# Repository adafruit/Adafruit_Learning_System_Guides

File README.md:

# Introduction

This is a collection of smaller programs and scripts to display "inline" in [Adafruit Learning System][learn] guides.

Adafruit is an Open Source company. To support Adafruit, please consider buying products at [adafruit.com](https://www.adafruit.com/).

Starting in 2023, guides using a specific Adafruit board will be placed in a subdirectory with that product name to reduce the number of directories under the main directory. If you are creating a new guide, please check if your Adafruit board falls into one of these groups and make your project code directory in the appropriate subfolder.

* Flora/
* ItsyBitsy/
* MagTag/
* MEMENTO/
* NeoTrellis/
* PyLeap/
* PyPortal/
* QTPy/
* Metro/ (all types)
* Matrix_Portal/
* Crickits/
* Gemma/ (both types)

If a new product or project group is contemplated, contact Learn moderators for guidance.

## Issues

Issues with guides should be reported in the guide itself under "Feedback? Corrections?"

## Make Your Own Guides

This repo is only for Adafruit approved Learning System Guides. If you'd like to write your own guide, see [Create your own content with Adafruit Playground!](https://learn.adafruit.com/adafruit-playground-notes).

## Contributing and Testing

For details on contributing for Adafruit approved guides, see the guide [Contribute to the Adafruit Learning System with Git and GitHub](https://learn.adafruit.com/contribute-to-the-adafruit-learning-system-with-git-and-github) and [Contribute to CircuitPython with Git and GitHub](https://learn.adafruit.com/contribute-to-circuitpython-with-git-and-github/github-personal-access-token).

The code here is checked by GitHub Actions against Pylint (for CircuitPython code) or the Arduino compilation process.

Code in directories containing a file called `.circuitpython.skip` will be skipped by Pylint checks.

Code in directories containing a `.[platformname].test` file, such as `.uno.test` will be compiled against the corresponding platform.

[learn]: https://learn.adafruit.com/

## Running pylint locally
Install a specific version of pylint under the name "pylint-learn":
```
pip install pipx
pipx install --suffix=-learn pylint==2.7.1
```
Then use the `pylint_check` script to run pylint on the files or directories
of your choice (note that your terminal *must* be in the top directory of
Adafruit_Learning_System_Guides, not a sub-directory):
```
./pylint_check CircuitPython_Cool_Project
```
## Licensing

Adafruit Learning System code files should have author and license information conforming to the open [SPDX specification](https://www.iso.org/standard/81870.html).
See [this page](https://learn.adafruit.com/contribute-to-the-adafruit-learning-system-with-git-and-github/add-author-and-license-information) for more.

Updated November 18, 2025

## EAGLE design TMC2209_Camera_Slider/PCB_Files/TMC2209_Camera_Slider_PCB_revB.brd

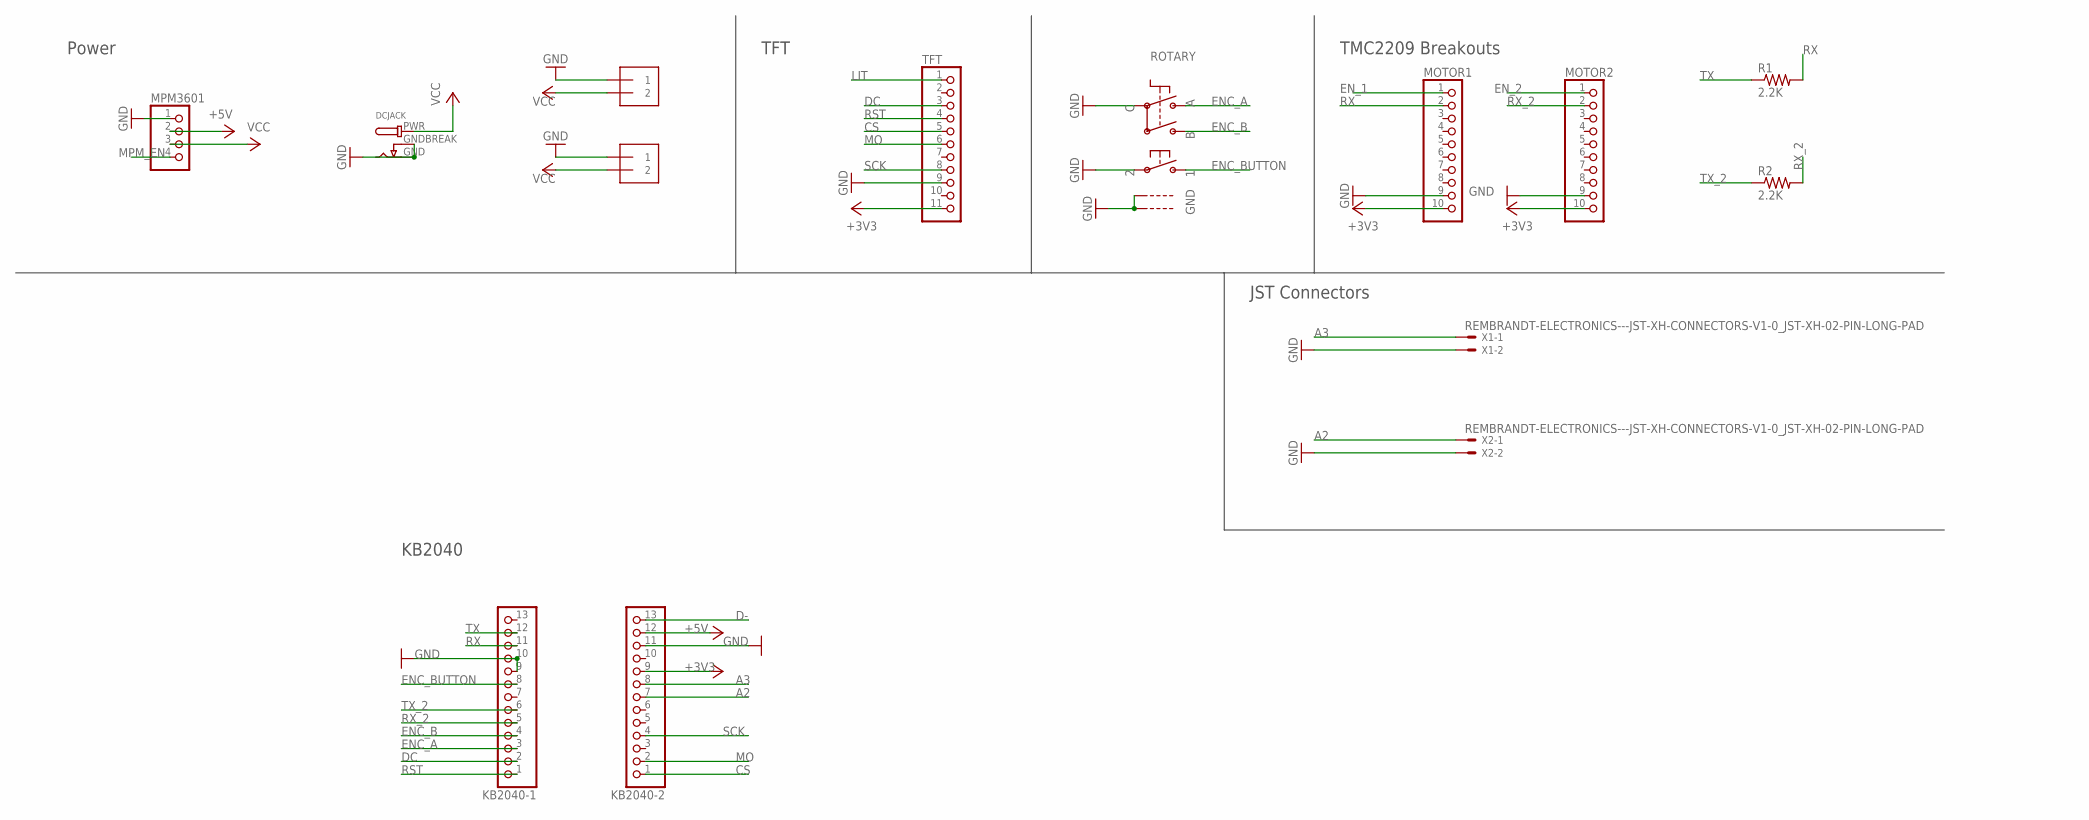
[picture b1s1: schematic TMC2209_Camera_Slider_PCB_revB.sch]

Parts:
DCJACK: DCBARRELPTH; DCJACK_2MM_PTH
J1, J2: 1X2-3.5MM
KB2040-1, KB2040-2: HEADER-1X13; 1X13_ROUND_70
MOTOR1, MOTOR2: HEADER-1X10; 1X10_OVAL
MPM3601: HEADER-1X4; 1X04_OVAL
R1, R2: 2.2K; 0309/12
ROTARY: ENCODER_PLUS_SWITCH_BOURNS_PEC11; PEC11+SWITCH
TFT: HEADER-1X11; 1X11_ROUND
X1, X2: REMBRANDT-ELECTRONICS---JST-XH-CONNECTORS-V1-0_JS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; REMBRANDT-ELECTRONICS---JST-XH-CONNECTORS-V1-0_JST-XH-02-PA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

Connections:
+3V3: KB2040-2.9, MOTOR1.10, MOTOR2.10, TFT.11
+5V: KB2040-2.12, MPM3601.2
A2: KB2040-2.7, X2.1
A3: KB2040-2.8, X1.1
CS: KB2040-2.1, TFT.5
D-: KB2040-2.13
DC: KB2040-1.2, TFT.3
ENC_A: KB2040-1.3, ROTARY.P$A
ENC_B: KB2040-1.4, ROTARY.P$B
ENC_BUTTON: KB2040-1.8, ROTARY.P$1
EN_1: MOTOR1.1
EN_2: MOTOR2.1
GND: DCJACK.GND, DCJACK.GNDBREAK, J1.1, J2.1, KB2040-1.9, KB2040-1.10, KB2040-2.11, MOTOR1.9, MOTOR2.9, MPM3601.1, ROTARY.P$2, ROTARY.P$C, ROTARY.P$GND1, ROTARY.P$GND2, TFT.9, X1.2, X2.2
LIT: TFT.1
MO: KB2040-2.2, TFT.6
MPM_EN: MPM3601.4
RST: KB2040-1.1, TFT.4
RX: KB2040-1.11, MOTOR1.2, R1.2
RX_2: KB2040-1.5, MOTOR2.2, R2.2
SCK: KB2040-2.4, TFT.8
TX: KB2040-1.12, R1.1
TX_2: KB2040-1.6, R2.1
VCC: DCJACK.PWR, J1.2, J2.2, MPM3601.3

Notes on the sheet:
Power
TFT
TMC2209 Breakouts
KB2040
JST Connectors

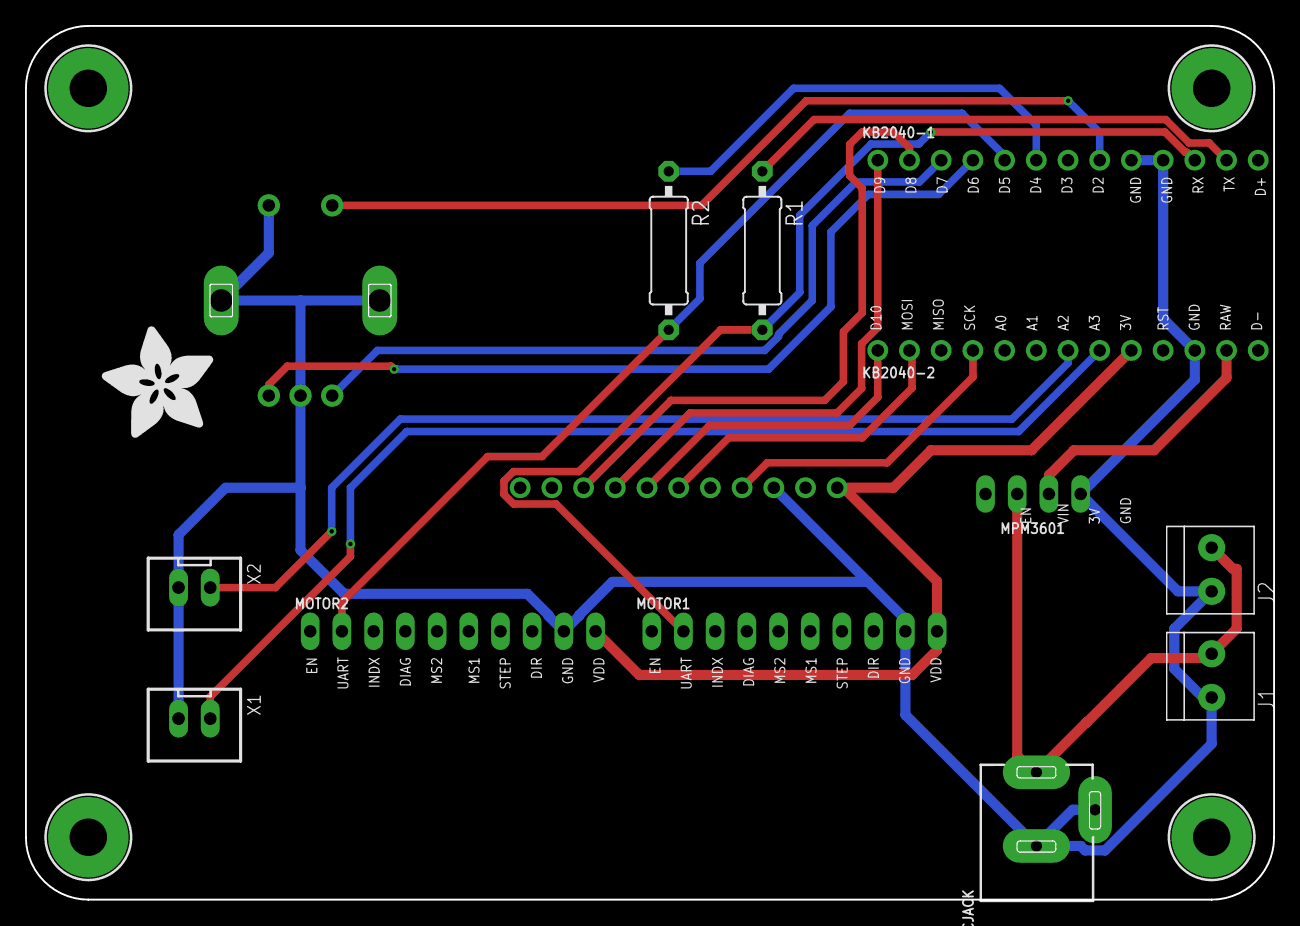
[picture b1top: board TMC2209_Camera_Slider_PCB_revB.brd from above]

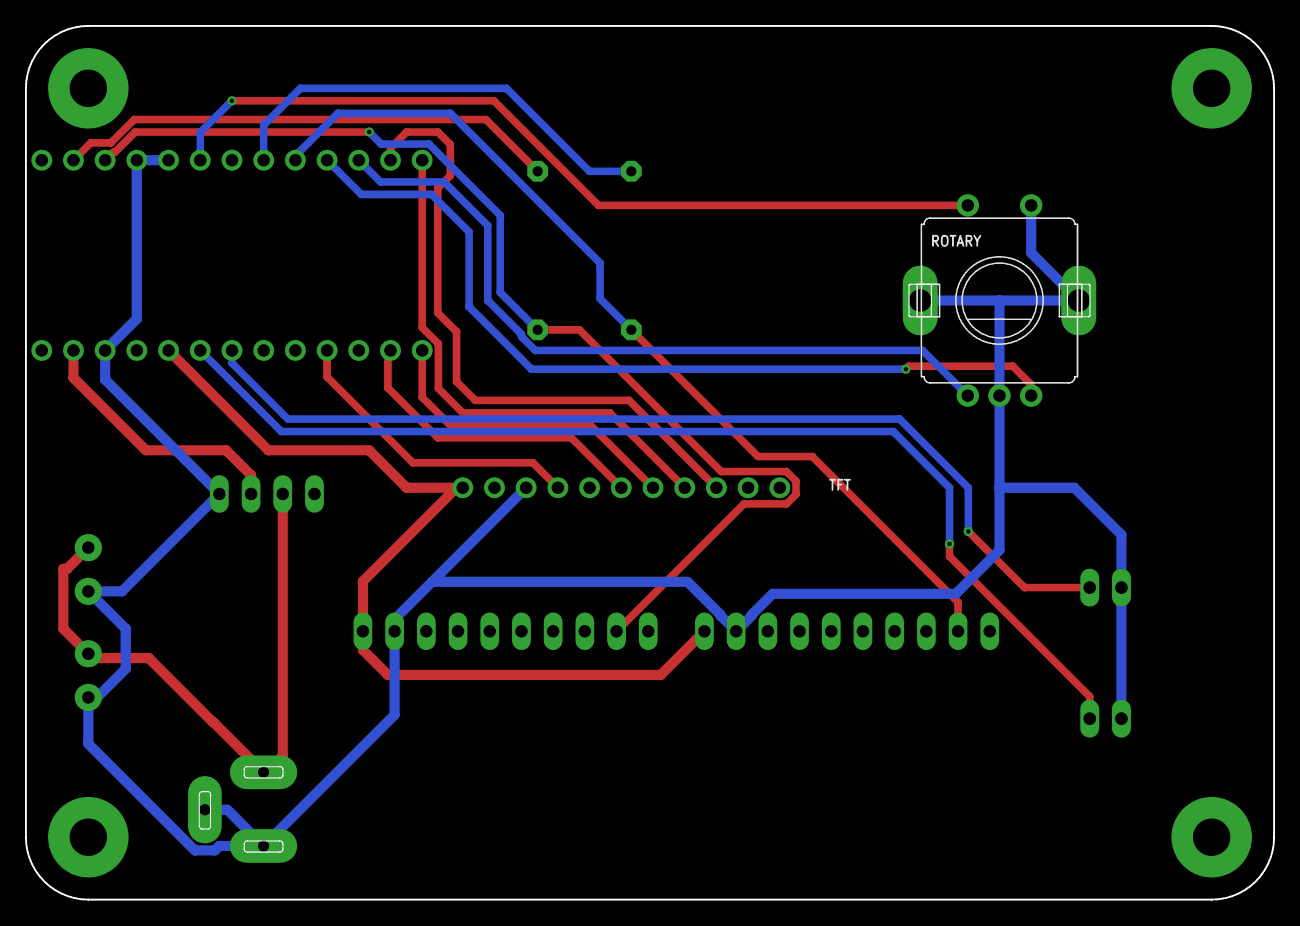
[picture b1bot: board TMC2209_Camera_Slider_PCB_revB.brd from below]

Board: 2 copper layers, 100.0 x 70.0 mm, 114 parts (51 on the bottom side), 18 nets.

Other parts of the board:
E$1, E$2, E$3, E$5: MOUNTINGHOLE_3.0_PLATED
PLABEL0, PLABEL94: PLABEL0
PLABEL1, PLABEL6: PLABEL6
PLABEL2: PLABEL2
PLABEL3: PLABEL3
PLABEL4: PLABEL4
PLABEL5: PLABEL5
PLABEL7, PLABEL95: PLABEL1
PLABEL8: PLABEL8
PLABEL9: PLABEL9
PLABEL10: PLABEL10
PLABEL11: PLABEL11
PLABEL12: PLABEL12
PLABEL13: PLABEL13
PLABEL14: PLABEL14
PLABEL15: PLABEL15
PLABEL16, PLABEL96: PLABEL16
PLABEL17: PLABEL17
PLABEL18: PLABEL18
PLABEL19: PLABEL19
PLABEL21: PLABEL21
PLABEL24: PLABEL24
PLABEL25: PLABEL25
PLABEL26: PLABEL26
PLABEL27: PLABEL27
PLABEL28: PLABEL28
PLABEL29: PLABEL29
PLABEL30: PLABEL30
PLABEL31: PLABEL31
PLABEL32: PLABEL32
PLABEL33: PLABEL33
PLABEL34: PLABEL34
PLABEL35: PLABEL35
PLABEL36: PLABEL36
PLABEL41: PLABEL41
PLABEL42: PLABEL42
PLABEL43: PLABEL43
PLABEL44: PLABEL44
PLABEL45: PLABEL45
PLABEL46: PLABEL46
PLABEL47: PLABEL47
PLABEL48: PLABEL48
PLABEL49: PLABEL49
PLABEL50: PLABEL50
PLABEL51: PLABEL51
PLABEL52: PLABEL52
PLABEL53: PLABEL53
PLABEL54: PLABEL54
PLABEL55: PLABEL55
PLABEL56: PLABEL56
PLABEL57: PLABEL57
PLABEL58: PLABEL58
PLABEL59: PLABEL59
PLABEL60: PLABEL60
PLABEL61: PLABEL61
PLABEL62: PLABEL62
PLABEL63: PLABEL63
PLABEL64: PLABEL64
PLABEL65: PLABEL65
PLABEL66: PLABEL66
PLABEL67: PLABEL67
PLABEL68: PLABEL68
PLABEL69: PLABEL69
PLABEL70: PLABEL70
PLABEL71: PLABEL71
PLABEL72: PLABEL72
PLABEL73: PLABEL73
PLABEL74: PLABEL74
PLABEL75: PLABEL75
PLABEL76: PLABEL76
PLABEL77: PLABEL77
PLABEL78: PLABEL78
PLABEL79: PLABEL79
PLABEL80: PLABEL80
PLABEL81: PLABEL81
PLABEL82: PLABEL82
PLABEL83: PLABEL83
PLABEL84: PLABEL84
PLABEL85: PLABEL85
PLABEL86: PLABEL86
PLABEL87: PLABEL87
PLABEL88: PLABEL88
PLABEL89: PLABEL89
PLABEL90: PLABEL90
PLABEL91: PLABEL91
PLABEL92: PLABEL92
PLABEL93: PLABEL93
PLABEL200: PLABEL200
PLABEL201: PLABEL201
PLABEL202: PLABEL202
PLABEL203: PLABEL203
PLABEL204: PLABEL204
U$1: ADAFRUIT_9MM

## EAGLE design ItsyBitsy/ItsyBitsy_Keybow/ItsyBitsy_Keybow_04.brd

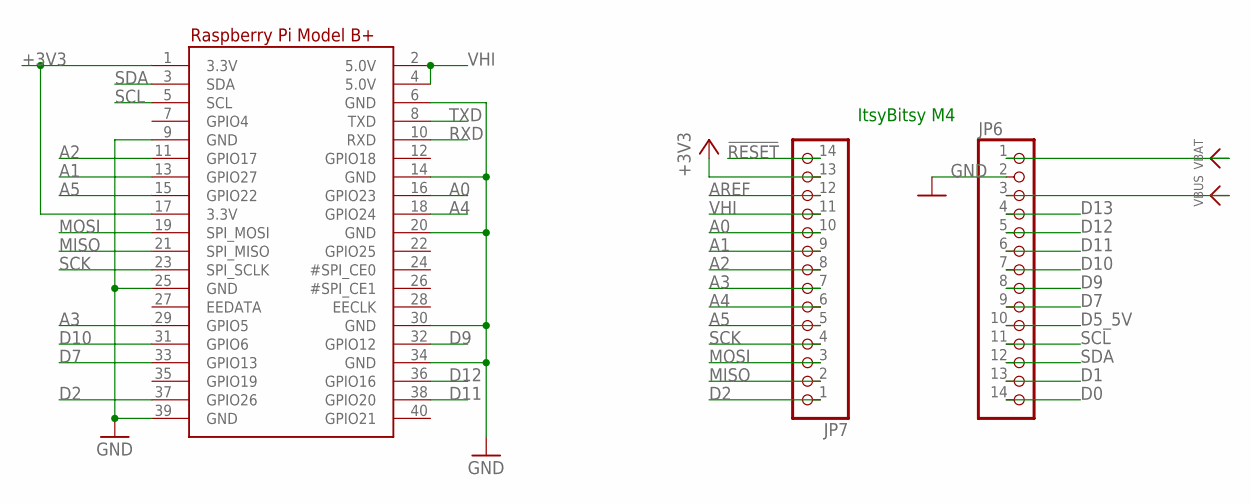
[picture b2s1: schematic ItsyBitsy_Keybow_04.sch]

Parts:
JP6, JP7: HEADER-1X14; 1X14_ROUND70
RPI1: RASPBERRYPI_BPLUS_BONNETNODIM; PI_BONNET_NODIM

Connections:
!RESET: JP7.14
+3V3: JP7.13, RPI1.1 (3.3V), RPI1.17 (3.3V)
A0: JP7.10, RPI1.16 (GPIO23)
A1: JP7.9, RPI1.13 (GPIO27)
A2: JP7.8, RPI1.11 (GPIO17)
A3: JP7.7, RPI1.29 (GPIO5)
A4: JP7.6, RPI1.18 (GPIO24)
A5: JP7.5, RPI1.15 (GPIO22)
AREF: JP7.12
D0: JP6.14
D1: JP6.13
D2: JP7.1, RPI1.37 (GPIO26)
D5_5V: JP6.10
D7: JP6.9, RPI1.33 (GPIO13)
D9: JP6.8, RPI1.32 (GPIO12)
D10: JP6.7, RPI1.31 (GPIO6)
D11: JP6.6, RPI1.38 (GPIO20)
D12: JP6.5, RPI1.36 (GPIO16)
D13: JP6.4
GND: JP6.2, RPI1.6 (GND), RPI1.9 (GND), RPI1.14 (GND), RPI1.20 (GND), RPI1.25 (GND), RPI1.30 (GND), RPI1.34 (GND), RPI1.39 (GND)
MISO: JP7.2, RPI1.21 (SPI_MISO)
MOSI: JP7.3, RPI1.19 (SPI_MOSI)
RXD: RPI1.10 (RXD)
SCK: JP7.4, RPI1.23 (SPI_SCLK)
SCL: JP6.11, RPI1.5 (SCL)
SDA: JP6.12, RPI1.3 (SDA)
TXD: RPI1.8 (TXD)
VBAT: JP6.1
VBUS: JP6.3
VHI: JP7.11, RPI1.2 (5.0V), RPI1.4 (5.0V)

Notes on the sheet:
ItsyBitsy M4

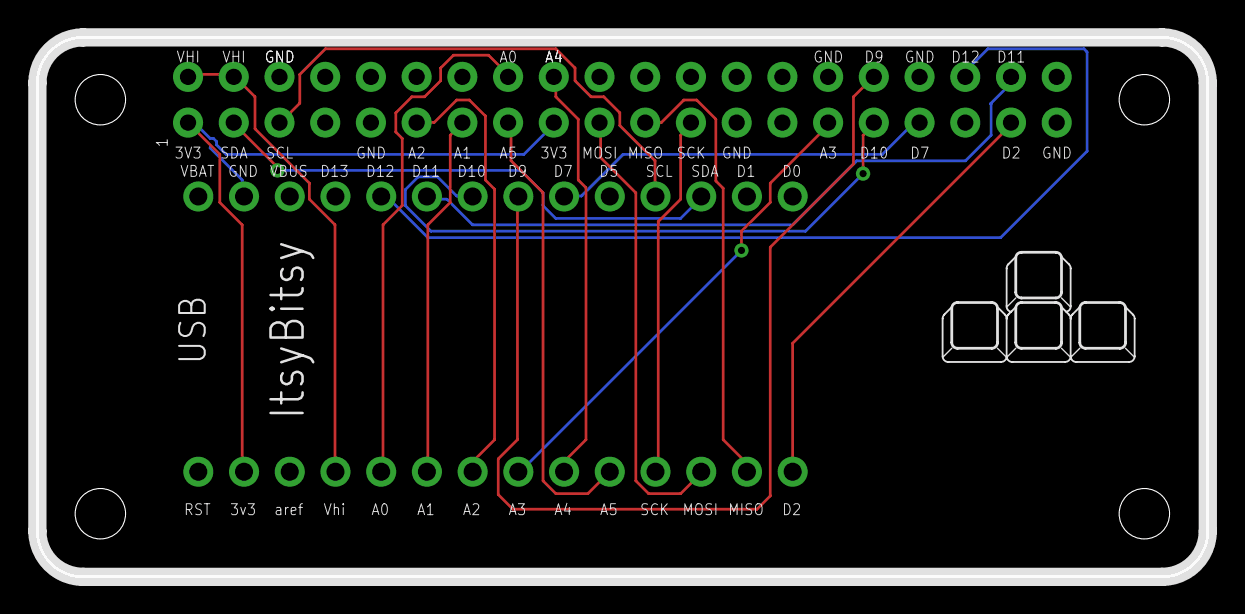
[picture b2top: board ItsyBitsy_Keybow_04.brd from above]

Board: 2 copper layers, 65.0 x 30.0 mm, 3 parts (0 on the bottom side), 20 nets.

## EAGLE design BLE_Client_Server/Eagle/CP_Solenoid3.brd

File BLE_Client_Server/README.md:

# Adafruit Learning System tutorial - A CircuitPython BLE Client & Server

Use Bluetooth to turn a server on and off and actively sense the server's status light

Follow the Adafruit learn guide here: https://learn.adafruit.com/circuitpython-ble-client-server/

Adafruit invests time and resources providing this open source code,
please support Adafruit and open-source hardware by purchasing
products from [Adafruit](https://www.adafruit.com)!
 
MIT license, project and code by rdagger

All text above, and the splash screen below must be included in any redistribution

-----------------------
If you are looking to make changes/additions, please use the GitHub Issues and Pull Request mechanisms.

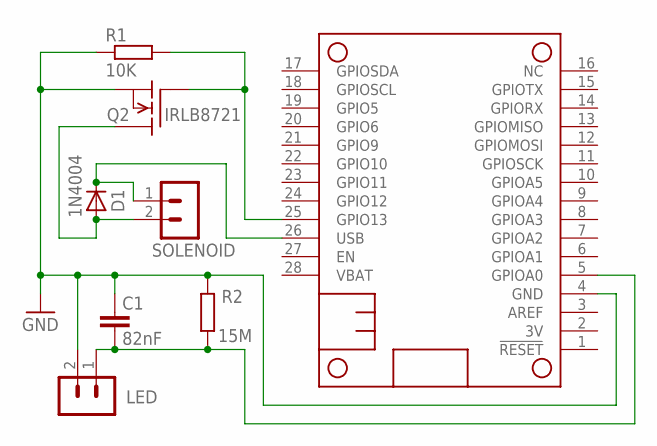
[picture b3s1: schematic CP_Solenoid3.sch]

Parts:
C1: 82nF; C025-025X050
D1: 1N4004; DO41-10
LED: B2B-PH-K-S
MS1: FEATHERWING_NODIM; FEATHERWING_DIM
Q2: IRLB8721; TO220
R1: 10K; 0207/10
R2: 15M; 0414/15
SOLENOID: B2B-PH-K-S

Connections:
GND: C1.1, LED.2, MS1.4 (GND), Q2.3 (S), R1.1, R2.2
unnamed: MS1.25 (GPIO13), Q2.1 (G), R1.2
unnamed: D1.A, Q2.2 (D), SOLENOID.2
unnamed: C1.2, LED.1, MS1.5 (GPIOA0), R2.1
USB: D1.C, MS1.26 (USB), SOLENOID.1

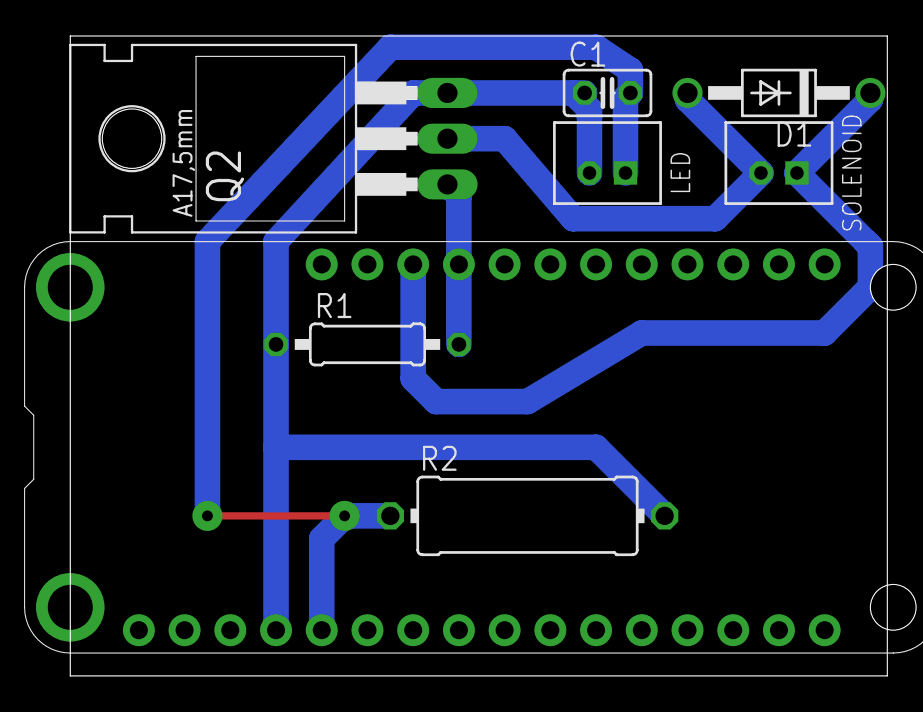
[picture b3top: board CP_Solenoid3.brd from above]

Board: 2 copper layers, 45.4 x 35.5 mm, 8 parts (0 on the bottom side), 5 nets.

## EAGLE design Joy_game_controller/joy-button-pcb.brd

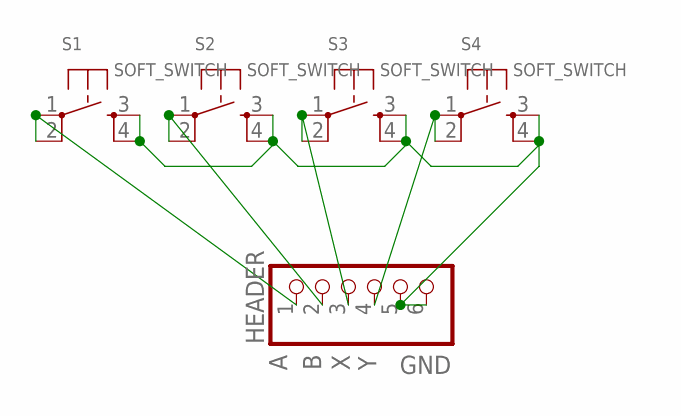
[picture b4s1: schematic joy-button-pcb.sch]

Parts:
HEADER: PINHD-1X6; 1X06
S1, S2, S3, S4: SOFT_SWITCH; 8MM_SWITCH

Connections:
A: HEADER.1, S1.1, S1.2 (P1)
B: HEADER.2, S2.1, S2.2 (P1)
GND: HEADER.5, HEADER.6, S1.3 (S), S1.4 (S1), S2.3 (S), S2.4 (S1), S3.3 (S), S3.4 (S1), S4.3 (S), S4.4 (S1)
X: HEADER.3, S3.1, S3.2 (P1)
Y: HEADER.4, S4.1, S4.2 (P1)

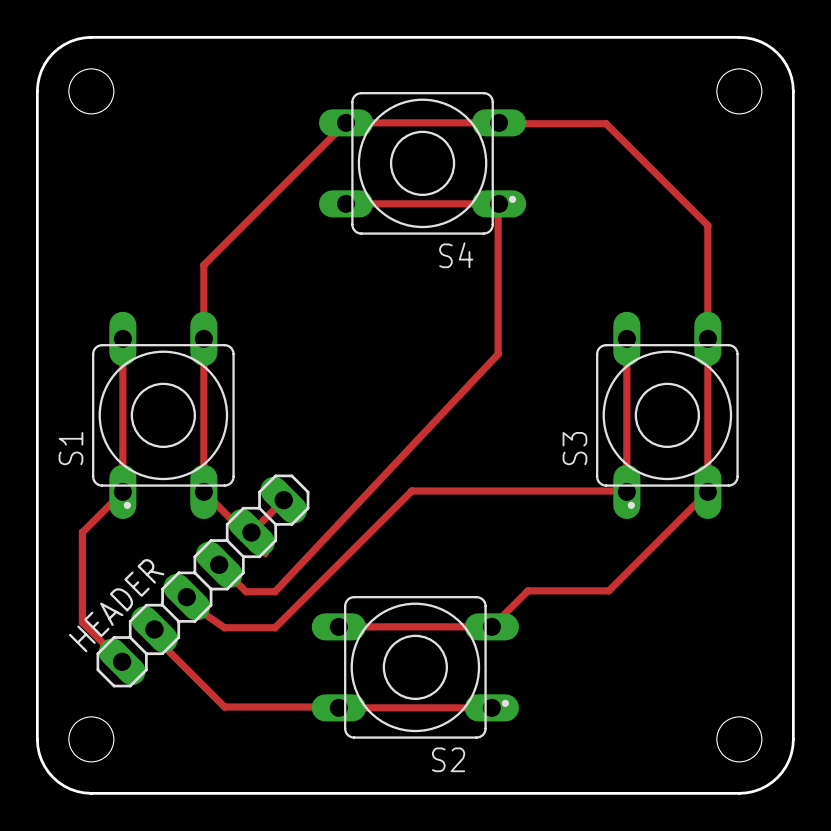
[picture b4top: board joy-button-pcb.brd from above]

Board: 2 copper layers, 42.0 x 42.0 mm, 5 parts (0 on the bottom side), 5 nets.

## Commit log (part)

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2025-12-09 Format code for consistency in code.py
2025-12-09 Delete NeoPixel_Gemma_Torch directory
    Code moved to https://github.com/adafruit/Adafruit_Learning_System_Guides/tree/main/Gemma/NeoPixel_Gemma_Torch
    Guide updated https://learn.adafruit.com/neopixel-flame-torch/code
2025-12-10 literature clock data files and book info tweak
2025-12-11 fruit jam logo
2025-12-11 png fruit jam logo
2025-12-13 update images
2025-12-15 Clone Introducing Gemma to Gemma/
    For guide changes
2025-12-15 Delete Introducing_Gemma_M0 directory
    Files moved to Gemma/
    Adafruit Introducing Germma M0 updated (1 file, most examples used CircuitPython Essentials examples)
2025-12-17 adding magtag menorah code and bitmap
2025-12-18 Fruit Jam greeting card maker
2025-12-18 add/expand comments about each code file
2025-12-18 add checkbox spritesheet
2026-01-11 CircuitPython Text Editor 2.4" FeatherWing
2026-01-21 Add support for Composite HID devices
2026-01-21 move atexit import up one to make pylint happy
2026-01-21 first commit epaper cam code
2026-01-21 magtag haiku viewer project files
2026-01-22 Update code.py JSON_URL
    There was a change to the folder structure at some point and the MagTag projects were moved inside a MagTag folder and this URL was broken. Corrected to reflect the new URL and tested on my device.
2026-01-22 move haiku loading code, add font file
2026-01-23 Fix Eink bonnet weather station for PIL >= 10
2026-01-26 code and example mp3s
2026-01-26 use PCF font instead of BDF
2026-01-27 update folder name
2026-01-27 adding bass synth code
2026-01-28 take out readonly
    causing problems with stability, filed issue on cp repo
2026-02-10 adding midi breath controller code
2026-02-10 reduced lag in joystick code
2026-02-11 Fix display brightness scaling during fade down
    Adjust brightness scaling for display fade effect, same as fade up, noted in guide feedback
2026-02-13 pylint warning for chip's challenge
2026-02-13 Fruit Jam Tiny Wiki server
2026-02-13 rename storage -> wiki_storage, reduce long lines, change title note on new page, use f-string instead of format, ignore some pylints
2026-02-13 move _escape_html() out of class to normal function.
2026-02-13 fix tiny_wiki typo
2026-02-16 Updating cpb glass lamp code
    Putting the CPB glass lamp code in a directory for learn.
2026-02-17 fixed SPDX error
2026-02-17 Update SPDX license and copyright information
2026-02-20 Disable discovery options in feather_bme280.yaml
    Avoid unauthorised fixed topics like esphome/ping/{device-name}
2026-02-20 adding rpi moonshine voice control neopixels
2026-02-20 add license, code format, add link to original code this was adapted from.
2026-02-21 Replace worldtimeapi.org with time.now/developer API
    Updates 16 files to replace the deprecated worldtimeapi.org time
    service with the new time.now/developer API endpoint.
    ⏺ | Guide | Filename | Change URL |
    |-------|----------|------------|
    | PicoW_YBox3 | PicoW_YBox3.ino |
    `https://time.now/developer/api/timezone/Etc/UTC` |
2026-02-23 fix --model-arch CLI arg
2026-02-23 remove unused generic callback
2026-02-24 update for BitmapLabel color_palette argument handling
2026-02-27 PyPortal Art Display
    IoT-connected art gallery that cycles through art, space, cats and dogs! Pull from image feeds or images from an SD card. Skip images with a tilt or shake. Tap the screen to change feeds. Customize y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
2026-02-27 PyPortal Art Display
    Removed consider-using-f-string — that check was added in pylint 2.8, so 2.7.1 doesn't recognize it and throws bad-option-value (exit code 123 even with a 10/10 score). Since 2.7.1 won't flag the %-f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
2026-02-27 Added code.py to it's own folder
    Added the folder PyPortal_Art_Display and put the code.py file in it.
2026-02-27 Refactored code.py
    Refactored code rather than blanket-disables
2026-02-27 global variable naming fix code.py
    adding invalid-name to each # pylint: disable=global-statement line catches it where it actually fires. All 10 global lines now have both disables.
2026-03-02 update arduino examples for 2025 magtag
2026-03-10 Update color constants to RGB565 format
2026-03-10 Update color constants to use RGB565 format
2026-03-11 Add initial implementation of camera control script
2026-03-11 Create settings.toml with initial configuration
    Add configuration settings for WiFi, API key, timezone, and AI prompt.
2026-03-11 Rename code.py to code.py
2026-03-11 Rename MEMENTO/Mementoflex/projectfiles/settings.toml to MEMENTO/Mementoflex/settings.toml
2026-03-14 adding 4.58" 320x960 rectangle bar display
    current qualia factory demo code was missing 4.58" 320x960 ADA# 5805 init / pulse / sync.
2026-03-16 code for blurry matrix clock
    analog clock with hour and minute hands over a
    gradient background that shifts through four palettes across
    the day.
2026-03-18 adding xteink x4 demos
    weather demo and bitmap display demo
2026-03-18 fix fstring
2026-03-19 Updating workflows to use actions using Node 24
2026-03-21 MagTag Daily Weather: Add battery state display
    Curious as to how long it's lasting, figured
    daily updates on battery state would be good.
    Also print battery state on the console.
2026-03-21 Fix missed renaming
2026-03-21 Fix extraneous import
2026-03-24 Adding code for midi neopixel visualizer
    code for the midi neopixel visualizer
2026-03-24 fix for pylint
    updating code to fix for pylint
2026-03-24 add simple arduino demo for ADS122C04
2026-03-30 adding fruit jam egg hunt maze game
2026-03-30 Create code.py
    Star Trek TNG Data Dispenser Prop - Environmental Monitor.
    Displays CO2, humidity, temperature and battery level as
    shaped colored bars on the ESP32-S3 Reverse TFT Feather
2026-03-30 Update code.py
    Six fixes for the CI failures
2026-03-31 refactor fixes to code.py
    @BlitzCityDIY excellent Claude updated and saved skills to memory:
    Updated:
    #1 — Expanded CI rules with exit code 123 behavior, full file-level disable list, inline disable thresholds, f-string requirement
    New:
    #8 — Code review patterns (STEMMA_I2C, imports at top, no defensive wrapping of required sensors, consolidate functions)
    #9 — ESP32-S3 Reverse TFT hardware gotchas (CP 9.2.9, TFT_I2C_POWER, D0/BOOT0 PinAlarm false triggers, light sleep workaround)
2026-03-31 pylint disables, Debouncer and import fixes
    excellent thanks @BlitzCityDIY @TheKitty
    here are the round of adjustments:
    1. f-string syntax error (line 2009)
    Extracted conditional to zoom_label variable
    2. DRV2605 shouldn't be optional import
    Moved to normal import adafruit_drv2605 at top
2026-03-31 f-string fix
    f-string fix No more instances left in the file
2026-03-31 too-many-branches fix
    Added too-many-branches to the existing inline disable on _update_lcars_graph
2026-04-01 Add README for fonts in version 2
2026-04-01 Fix ppylint errors
2026-04-01 Fix one scope issue not caught previously
2026-04-01 add import and init for pre-2024 bonnet
2026-04-07 update circuitpython dvi sock demo
    received guide feedback that this example throws a memoryerror with current circuitpython on the original pico. updated to only run some of the examples for the rp2040 pico, while still running all o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
2026-04-08 first commit Onekey sketch and web page
2026-04-08 moved ino file out of dir
2026-04-10 Swap I2SOut pins for audio output
    Call I2SOut with correct pin order
2026-04-13 add code for esp-now walkie talkies
2026-04-16 added licensing info
2026-04-16 added corrected license info
2026-04-20 adding tetris mit green building code
2026-04-21 add font file for tetris
2026-04-24 matrixportal world cup code and graphics
2026-04-24 ran older version of pylint locally, fixed errors
2026-04-26 arduino_cron.yml: fix
2026-04-26 arduino_cron.yml: check-upated 'if:' is not needed
2026-04-30 Create code.py
    Initial commit
2026-04-30 Update code.py
    Fixed pylint issues.
2026-04-30 Update code.py
    Added missing final newline
2026-05-05 adding Sensor_Locked_Secrets
2026-05-05 fix gps typo
2026-05-05 fix licenses
2026-05-07 clue ble beacon
    clue ble remote code
2026-05-07 BLE beacon ears
    QTPy code to make into a BLE receiver
2026-05-07 Update code.py
    Removed unused import neopixel line
    32339 bytes (16 bytes smaller, slightly more headroom under the cliff)
    Lint clean even with unused-import enforced (Adafruit CI doesn't disable that one — my local config did, mistake on my part)
    Behavior unchanged — neopixel was never actually used here, only inside pixel_zones.py
2026-05-09 fixes to code, main and added battery.py
    applied fixes to code, removed main and added battery.py
2026-05-09 code.py format fixes
    formatting issue fixes in code.py
2026-05-13 first commit cluetooth code
2026-05-13 fix pylint error
2026-05-16 Changed order of NeoPixel lighting
    NeoPixel currently holds on to cyan or pink color after the connection test, instead of indicating water level in the test. I moved the NeoPixel color display down, so that the water level status col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
2026-05-21 add embodiment kit files
2026-05-21 fix remaining spdx headers
2026-05-21 refactor methods to functions. pylint disable for too large functions in CLI script
2026-05-21 remove broad except, black format CLI script
2026-05-28 prop it game code
    adding code for prop it game
2026-05-28 lint
2026-06-08 adding final code and sfx files
2026-06-08 line too long
2026-06-12 Pi video feedback project
2026-06-14 Minecraft code
    code for the minecraft gps compass
2026-06-18 Do not ignore RuntimeError when doing pin finding
2026-06-21 minecraft GPS compass code
    minecraft GPS compass code
2026-06-22 code fixes
    1. MAX17048 wrapped in try/except
    2. Blocking time.sleep in the loop — replaced the blocking message flashes with a non-blocking flash-message system
    3. adafruit_debouncer.Button (mc_compass) — replaced my hand-rolled two-tier hold timing
    4. recalibration no longer deletes the whole file. It now rewrites settings.toml keeping every non-MAG_ line, clearing only the calibration keys this project owns.
2026-06-23 adding code for circuitpython chiptune player
2026-06-23 add header comment
2026-06-24 Fix for hold-to-save
    Fix hold-to-save: time the hold from the debounced level, not edge flags
    The Button.pressed/released one-shot edge flags intermittently dropped a
    press, so hold-to-save would fall through and register as a short tap
    (switching mode instead of saving). poll_button now reads the debounced
    level (button.value) and detects the press/release edges itself, timing
    the hold with time.monotonic(). This also survives the ~300-500 ms loop
2026-06-24 Set file mode to 100644 (remove executable bit)
2026-06-24 CPB Morse code paddle project code
2026-06-24 use keypad instead of adafruit_debouncer, change paddle to key

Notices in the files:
parts and their libraries:
microbuilder: This work is placed in the public domain, and may be freely used for commercial and non-commercial work with the following conditions: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
